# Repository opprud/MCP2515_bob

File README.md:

# MCP2515_bob
MCP2515 CAN controller breakout board

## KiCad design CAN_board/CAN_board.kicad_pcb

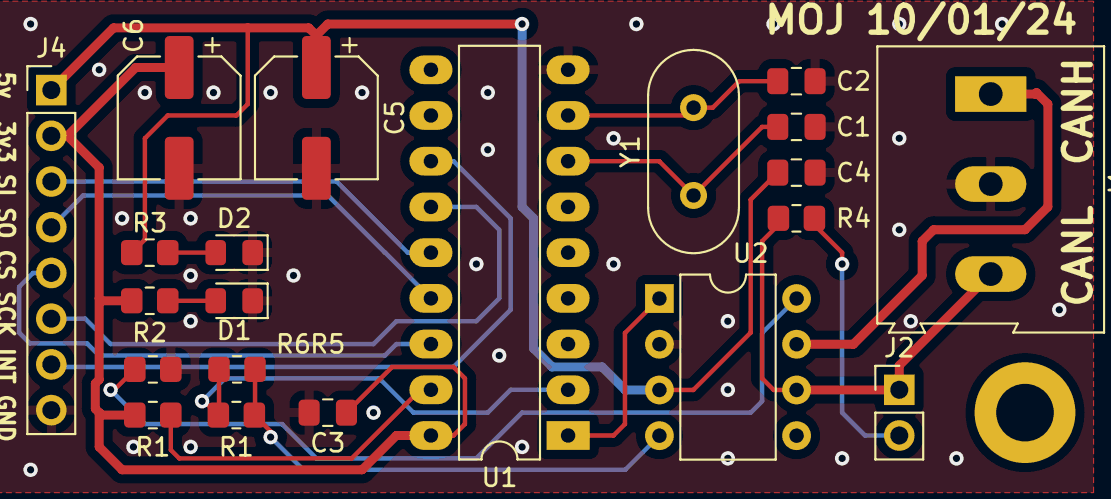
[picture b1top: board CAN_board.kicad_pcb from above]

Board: 2 copper layers, 21 parts (0 on the bottom side), 20 nets.

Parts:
C1, C2: 15p; C_0805_2012Metric_Pad1.18x1.45mm_HandSolder
C3, C4: 100n; C_0805_2012Metric_Pad1.18x1.45mm_HandSolder
C5, C6: 47u; CP_Elec_6.3x5.4
D1, D2: LED; LED_0805_2012Metric_Pad1.15x1.40mm_HandSolder
J1: Screw_Terminal_01x03; TerminalBlock_Altech_AK300-3_P5.00mm
J2: Term; PinHeader_1x02_P2.54mm_Vertical
J4: Conn_01x08_Pin; PinHeader_1x08_P2.54mm_Vertical
R1: R; R_0805_2012Metric_Pad1.20x1.40mm_HandSolder
R1#2: 10k; R_0805_2012Metric_Pad1.20x1.40mm_HandSolder
R2: 820; R_0805_2012Metric_Pad1.20x1.40mm_HandSolder
R3: 1k2; R_0805_2012Metric_Pad1.20x1.40mm_HandSolder
R4: 120; R_0805_2012Metric_Pad1.20x1.40mm_HandSolder
R5: 1k5; R_0805_2012Metric_Pad1.20x1.40mm_HandSolder
R6: 100; R_0805_2012Metric_Pad1.20x1.40mm_HandSolder
U1: MCP2515; DIP-18_W7.62mm_LongPads
U2: MCP2551; DIP-8_W7.62mm
Y1: 20MHz; Crystal_HC49-U_Vertical

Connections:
//INT: J4.7, U1.12 (~INT)
GND: C1.2, C2.2, C3.2, C4.2, C5.2, C6.2, D1.1 (K), D2.1 (K), J1.2, J4.8, R6.2, U1.9 (VSS), U2.2 (VSS)
unnamed: D1.2 (A), R2.2
unnamed: D2.2 (A), R3.2
unnamed: J1.1, U2.7 (CANH)
unnamed: J1.3, J2.1, R4.1, U2.6 (CANL)
unnamed: J2.2, R4.2
unnamed: J4.3, U1.14 (SI)
unnamed: J4.4, U1.15 (SO)
unnamed: J4.5, U1.16 (~CS)
unnamed: J4.6, U1.13 (SCK)
unnamed: C2.1, U1.8 (OSC1), Y1.2
unnamed: C1.1, U1.7 (OSC2), Y1.1
unnamed: R1.1, R5.1, U1.2 (RXCAN)
unnamed: U1.1 (TXCAN), U2.1 (TXD)
unnamed: R1#2.2, U1.17 (~RESET)
unnamed: R1.2, R5.2, U2.4 (RXD)
unnamed: R6.1, U2.8 (Rs)
VCC: C3.1, C6.1, J4.2, R1#2.1, R2.1, U1.18 (VDD)
VCCQ: C4.1, C5.1, J4.1, R3.1, U2.3 (VDD)

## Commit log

2024-01-30 added initial design
